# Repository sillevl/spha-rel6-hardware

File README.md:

# Six-channel relay module

SPHA six-channel relay/light-output module.

## Design files

- `relay-module-light.kicad_pro` — KiCad project
- `relay-module-light.kicad_sch` — top-level schematic
- `relay-module-light.kicad_pcb` — PCB layout
- Additional `.kicad_sch` files — hierarchical schematic sheets
- `models/` — project-specific 3D and mechanical models

## Working with the project

Open the `.kicad_pro` file in KiCad. The design includes files originating from an older KiCad workflow; review schematic links, footprints, design rules, zones, and manufacturing outputs after any conversion or upgrade.

KiCad source files and project-specific libraries are the source of truth. Generated BOM, Gerber, assembly, and fabrication-house outputs are excluded from the repository; regenerate and verify them before manufacturing.

## Repository notes

Temporary KiCad state, locks, autosaves, and backup directories are excluded by `.gitignore`. Board revision, tested KiCad version, manufacturing revision, and hardware/firmware compatibility still need to be recorded when provenance is confirmed.

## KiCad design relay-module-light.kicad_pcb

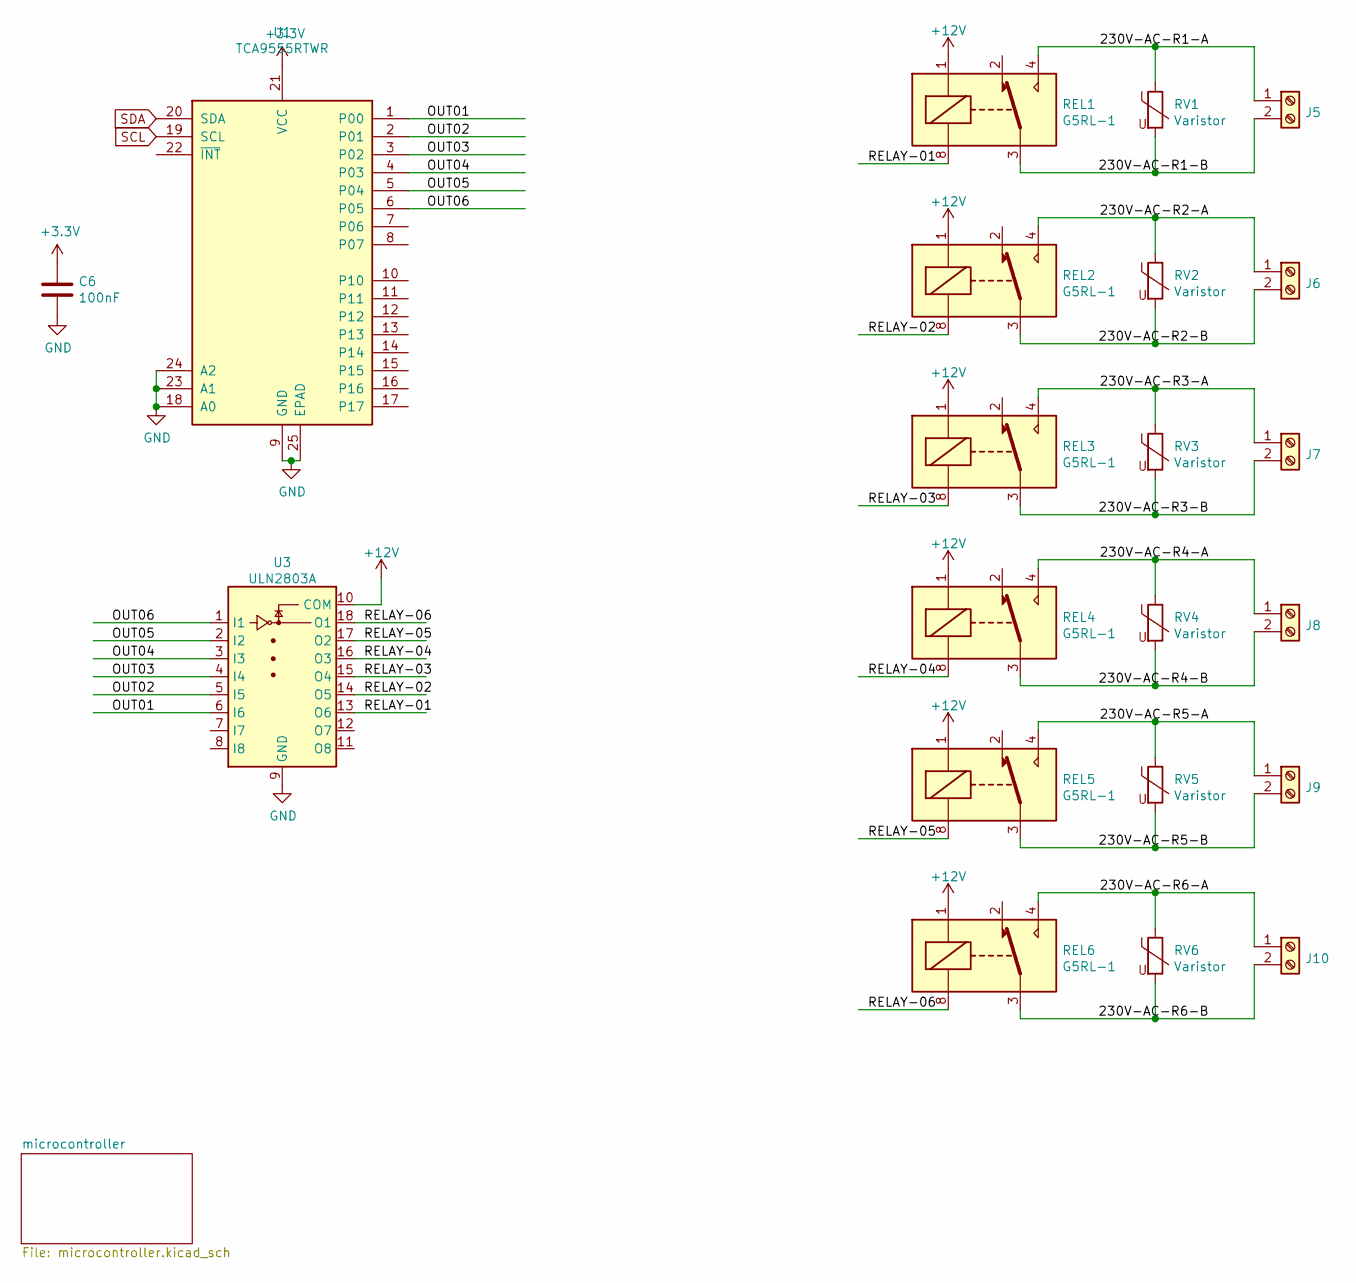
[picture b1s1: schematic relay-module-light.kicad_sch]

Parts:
C6: 100nF; C_0603_1608Metric_Pad1.05x0.95mm_HandSolder
J5, J6, J7, J8, J9, J10: Screw_Terminal_01x02; TerminalBlock_MetzConnect_Type175_RT02702HBLC_1x02_P7.50mm_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
REL1, REL2, REL3, REL4, REL5, REL6: G5RL-1; Relay_DPDT_Omron_G2RL
RV1, RV2, RV3, RV4, RV5, RV6: Varistor; RV_Disc_D7mm_W4mm_P5mm
U1: TCA9555RTWR; WQFN-24-1EP_4x4mm_P0.5mm_EP2.45x2.45mm
U3: ULN2803A; SOP-18_7x12.5mm_P1.27mm

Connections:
+3V3: C6.1, U1.21 (VCC); also elsewhere on the board
+12V: REL1.1, REL2.1, REL3.1, REL4.1, REL5.1, REL6.1, U3.10 (COM); also elsewhere on the board
/230V-AC-R1-A: J5.1, REL1.4, REL1.5, RV1.1
/230V-AC-R1-B: J5.2, REL1.3, REL1.6, RV1.2
/230V-AC-R2-A: J6.1, REL2.4, REL2.5, RV2.1
/230V-AC-R2-B: J6.2, REL2.3, REL2.6, RV2.2
/230V-AC-R3-A: J7.1, REL3.4, REL3.5, RV3.1
/230V-AC-R3-B: J7.2, REL3.3, REL3.6, RV3.2
/230V-AC-R4-A: J8.1, REL4.4, REL4.5, RV4.1
/230V-AC-R4-B: J8.2, REL4.3, REL4.6, RV4.2
/230V-AC-R5-A: J9.1, REL5.4, REL5.5, RV5.1
/230V-AC-R5-B: J9.2, REL5.3, REL5.6, RV5.2
/230V-AC-R6-A: J10.1, REL6.4, REL6.5, RV6.1
/230V-AC-R6-B: J10.2, REL6.3, REL6.6, RV6.2
/OUT01: U1.1 (P00), U3.6 (I6)
/OUT02: U1.2 (P01), U3.5 (I5)
/OUT03: U1.3 (P02), U3.4 (I4)
/OUT04: U1.4 (P03), U3.3 (I3)
/OUT05: U1.5 (P04), U3.2 (I2)
/OUT06: U1.6 (P05), U3.1 (I1)
/RELAY-01: REL1.8, U3.13 (O6)
/RELAY-02: REL2.8, U3.14 (O5)
/RELAY-03: REL3.8, U3.15 (O4)
/RELAY-04: REL4.8, U3.16 (O3)
/RELAY-05: REL5.8, U3.17 (O2)
/RELAY-06: REL6.8, U3.18 (O1)
unnamed: REL1.2, REL1.7
unnamed: REL2.2, REL2.7
unnamed: REL3.2, REL3.7
unnamed: REL4.2, REL4.7
unnamed: REL5.2, REL5.7
unnamed: REL6.2, REL6.7
SCL: U1.19 (SCL); also elsewhere on the board
SDA: U1.20 (SDA); also elsewhere on the board

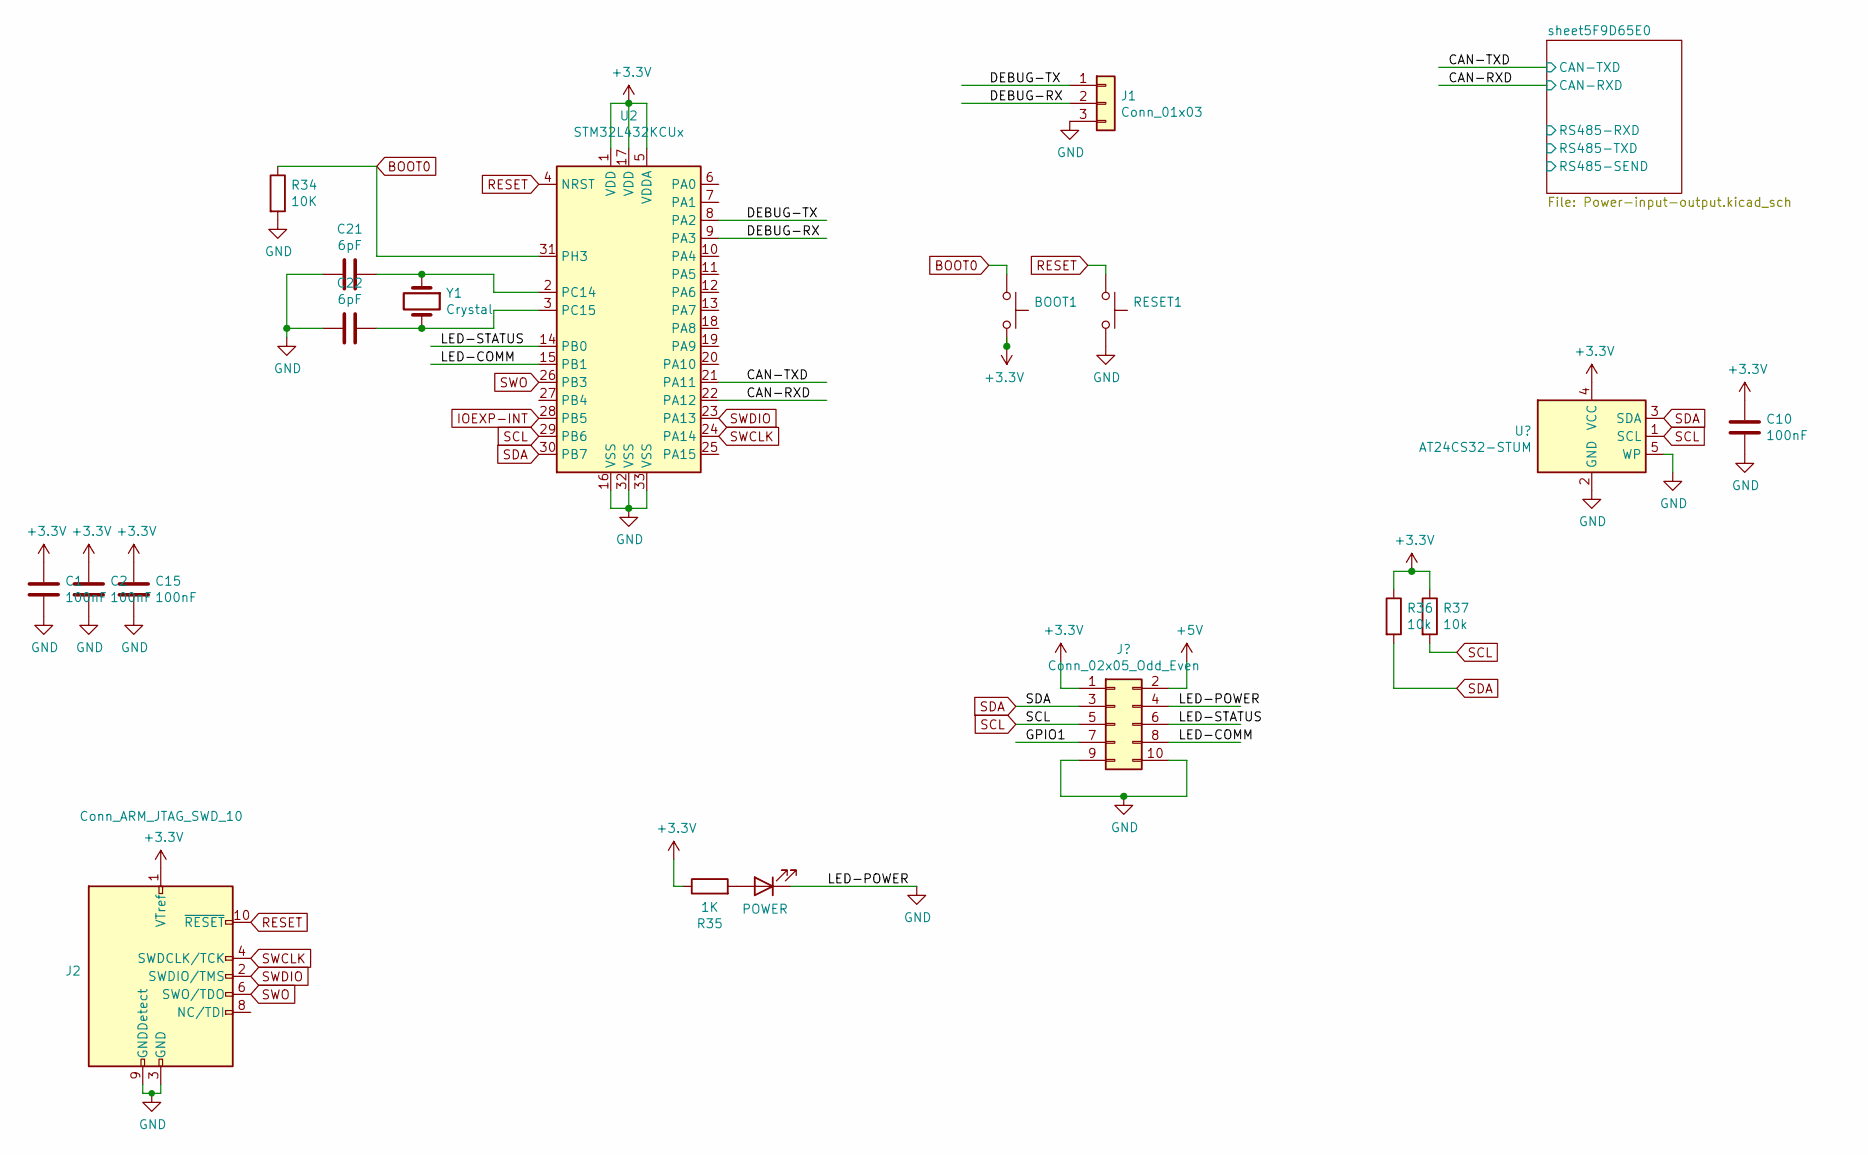
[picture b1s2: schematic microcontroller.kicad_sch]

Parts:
BOOT1: BOOT0; SW_SPST_B3U-1000P
C1, C2, C10, C15: 100nF; C_0603_1608Metric_Pad1.05x0.95mm_HandSolder
C21, C22: 6pF; C_0603_1608Metric_Pad1.05x0.95mm_HandSolder
J1: Conn_01x03; PinHeader_1x03_P2.54mm_Vertical
J2: Conn_ARM_JTAG_SWD_10; PinHeader_2x05_P1.27mm_Vertical_SMD
LED1: POWER; LED_0603_1608Metric_Pad1.05x0.95mm_HandSolder
R34: 10K; C_0603_1608Metric_Pad1.05x0.95mm_HandSolder
R35: 1K; C_0603_1608Metric_Pad1.05x0.95mm_HandSolder
R36, R37: 10k; C_0603_1608Metric_Pad1.05x0.95mm_HandSolder
RESET1: RESET; SW_SPST_B3U-1000P
U2: STM32L432KCUx; QFN-32-1EP_5x5mm_P0.5mm_EP3.45x3.45mm
Y1: Crystal; Crystal_SMD_MicroCrystal_CC7V-T1A-2Pin_3.2x1.5mm

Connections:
+3V3: BOOT1.2, C1.1, C2.1, C10.1, C15.1, J2.1 (VTref), R35.1, R36.1, R37.1, U2.1 (VDD), U2.5 (VDDA), U2.17 (VDD); also elsewhere on the board
/microcontroller/CAN-RXD: U2.22 (PA12); also elsewhere on the board
/microcontroller/CAN-TXD: U2.21 (PA11); also elsewhere on the board
/microcontroller/DEBUG-RX: J1.2, U2.9 (PA3)
/microcontroller/DEBUG-TX: J1.1, U2.8 (PA2)
/microcontroller/LED-COMM: U2.15 (PB1); also elsewhere on the board
/microcontroller/LED-STATUS: U2.14 (PB0); also elsewhere on the board
BOOT0: BOOT1.1, R34.1, U2.31 (PH3)
unnamed: C21.1, U2.2 (PC14), Y1.1
unnamed: C22.1, U2.3 (PC15), Y1.2
unnamed: LED1.2 (A), R35.2
RESET: J2.10 (~RESET~), RESET1.1, U2.4 (NRST)
SCL: R37.2, U2.29 (PB6); also elsewhere on the board
SDA: R36.2, U2.30 (PB7); also elsewhere on the board
SWCLK: J2.4 (SWDCLK/TCK), U2.24 (PA14)
SWDIO: J2.2 (SWDIO/TMS), U2.23 (PA13)
SWO: J2.6 (SWO/TDO), U2.26 (PB3)

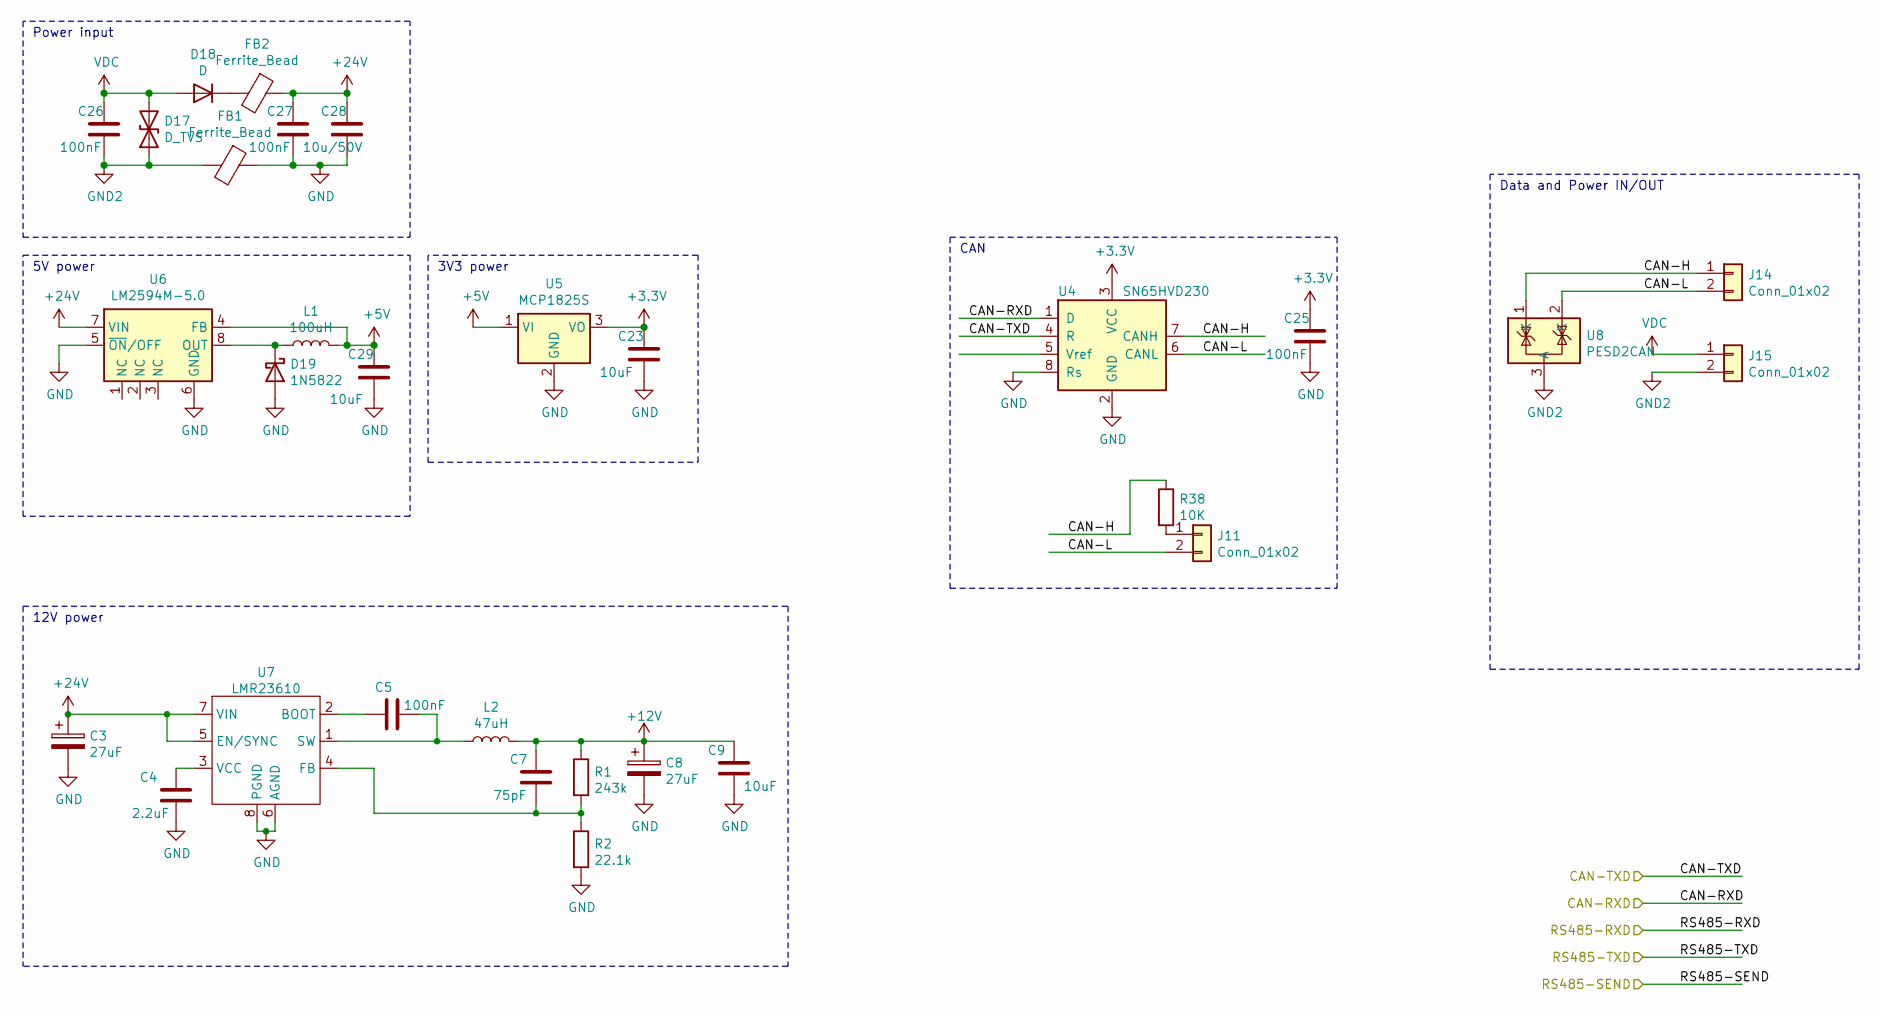
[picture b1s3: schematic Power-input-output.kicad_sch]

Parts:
C3, C8: 27uF; CP_Elec_6.3x5.7
C4: 2.2uF; C_0603_1608Metric
C5, C25, C26, C27: 100nF; C_0603_1608Metric
C7: 75pF; C_0603_1608Metric
C9, C23, C29: 10uF; C_1206_3216Metric
C28: 10u/50V; C_1206_3216Metric
D17: D_TVS; D_SMB
D18: D; D_SMA
D19: 1N5822; D_SOD-123
FB1, FB2: Ferrite_Bead; R_0603_1608Metric
J11: Conn_01x02; PinHeader_1x02_P2.54mm_Vertical
J14, J15: Conn_01x02; TerminalBlock_bornier-2_P5.08mm
L1: 100uH; L_Wuerth_WE-PD2-Typ-MS
L2: 47uH; L_12x12mm_H8mm
R1: 243k; R_0603_1608Metric
R2: 22.1k; R_0603_1608Metric
R38: 10K; R_0603_1608Metric
U4: SN65HVD230; SOIC-8_3.9x4.9mm_P1.27mm
U5: MCP1825S; SOT-223
U6: LM2594M-5.0; SOIC-8_3.9x4.9mm_P1.27mm
U7: LMR23610; HSOIC-8
U8: PESD2CAN; SOT-23

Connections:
+3V3: C23.1, C25.1, U4.3 (VCC), U5.3 (VO); also elsewhere on the board
+5V: C29.1, L1.2, U5.1 (VI), U6.4 (FB); also elsewhere on the board
+12V: C7.2, C8.1, C9.1, L2.2, R1.1; also elsewhere on the board
+24V: C3.1, C27.1, C28.1, FB2.1, U6.7 (VIN), U7.5 (EN/SYNC), U7.7 (VIN)
/microcontroller/CAN-RXD: U4.1 (D); also elsewhere on the board
/microcontroller/CAN-TXD: U4.4 (R); also elsewhere on the board
/microcontroller/sheet5F9D65E0/CAN-H: J14.1, R38.1, U4.7 (CANH), U8.1 (K)
/microcontroller/sheet5F9D65E0/CAN-L: J11.2, J14.2, U4.6 (CANL), U8.2 (K)
GND2: C26.2, D17.1 (A1), FB1.2, J15.2, U8.3 (A)
unnamed: C4.1, U7.3 (VCC)
unnamed: C5.1, U7.2 (BOOT)
unnamed: C5.2, L2.1, U7.1 (SW)
unnamed: C7.1, R1.2, R2.1, U7.4 (FB)
unnamed: D18.1 (K), FB2.2
unnamed: D19.1 (K), L1.1, U6.8 (OUT)
unnamed: J11.1, R38.2
VDC: C26.1, D17.2 (A2), D18.2 (A), J15.1

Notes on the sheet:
12V power
3V3 power
CAN
5V power
Data and Power IN/OUT
Power input

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
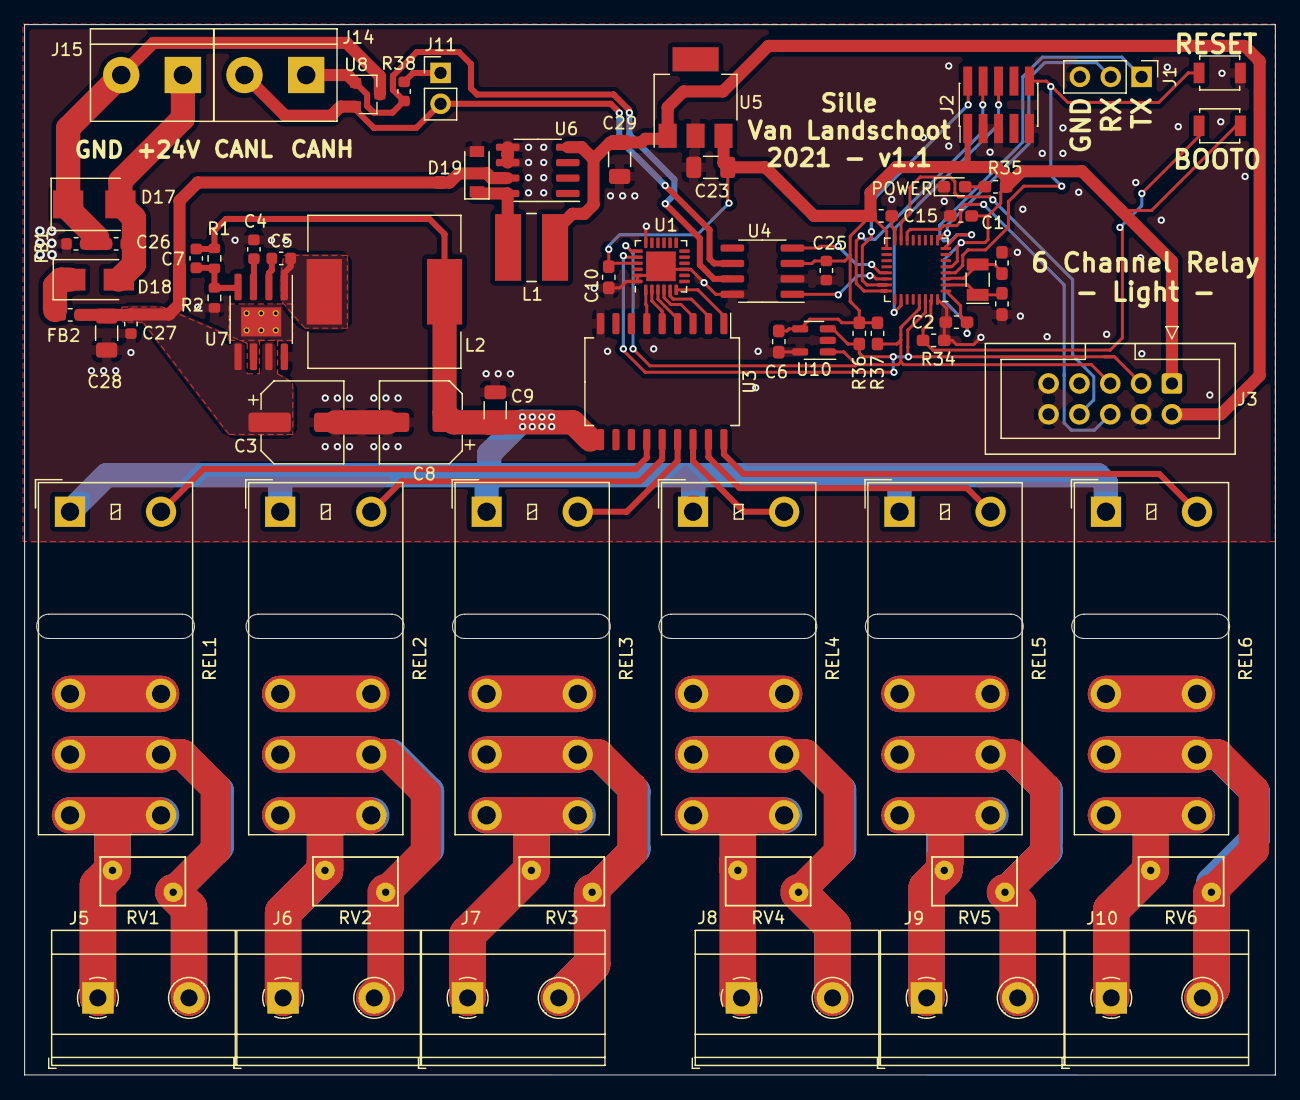
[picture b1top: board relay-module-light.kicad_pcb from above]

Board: 2 copper layers, 103.0 x 86.5 mm, 70 parts (0 on the bottom side), 62 nets.

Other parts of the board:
J3: Conn_02x05_Odd_Even; IDC-Header_2x05_P2.54mm_Vertical
U10: AT24CS32-STUM; SOT-23-5

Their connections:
+3V3: J3.1, U10.4 (VCC); also elsewhere on the board
+5V: J3.2; also elsewhere on the board
/microcontroller/LED-COMM: J3.8; also elsewhere on the board
/microcontroller/LED-STATUS: J3.6; also elsewhere on the board
SCL: J3.5, U10.1 (SCL); also elsewhere on the board
SDA: J3.3, U10.3 (SDA); also elsewhere on the board
